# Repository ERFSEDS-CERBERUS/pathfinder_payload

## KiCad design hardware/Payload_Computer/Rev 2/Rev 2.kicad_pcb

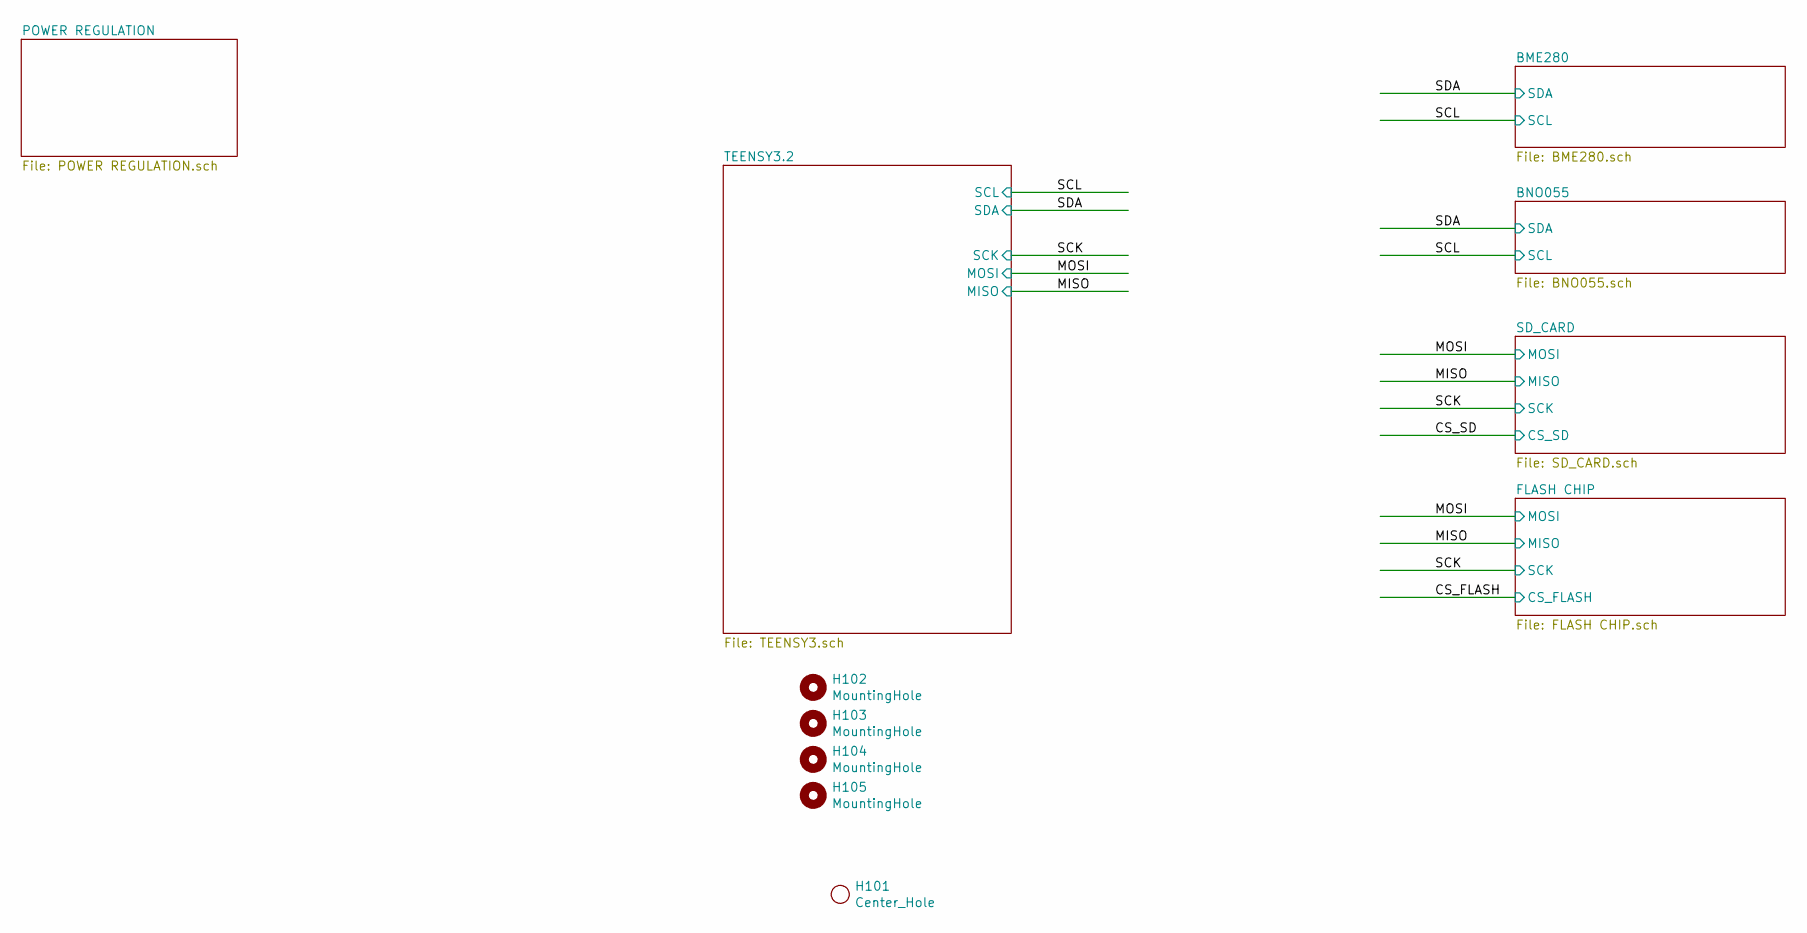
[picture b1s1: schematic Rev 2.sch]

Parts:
H101: Center_Hole; Center_hole
H102, H103, H104, H105: MountingHole; MountingHole_3.5mm

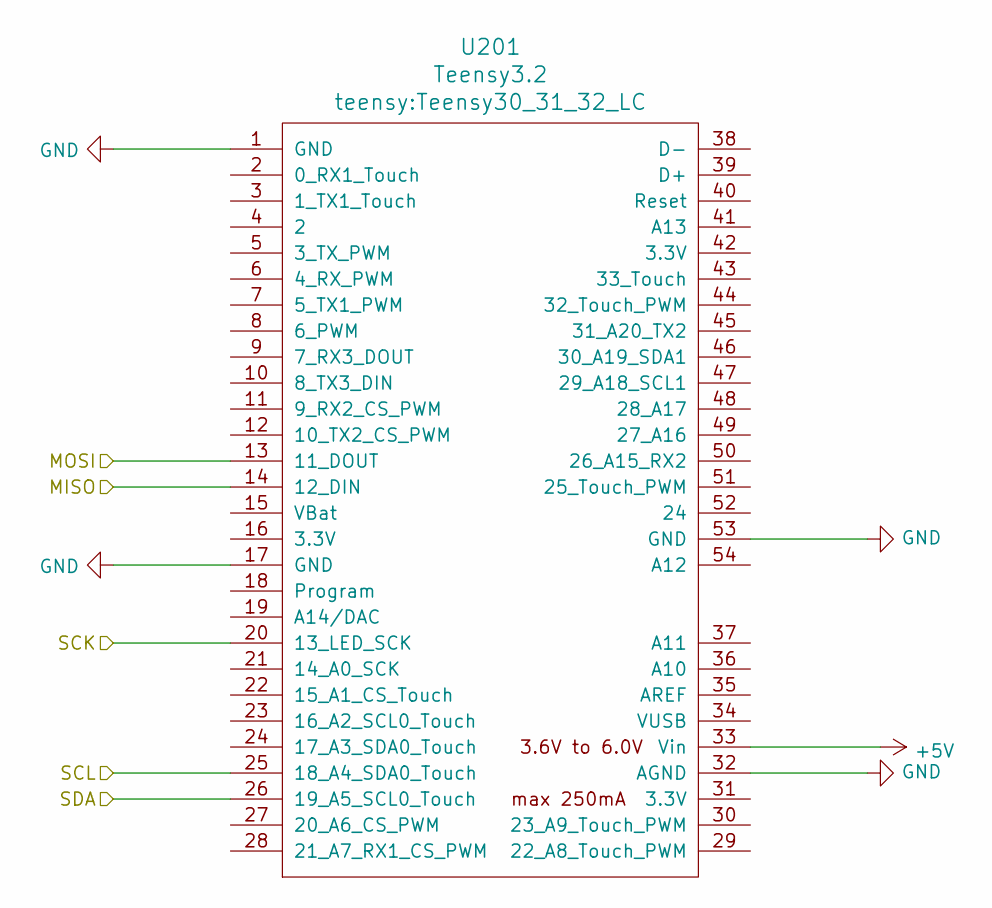
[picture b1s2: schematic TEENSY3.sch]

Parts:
U201: Teensy3.2; Teensy30_31_32_LC

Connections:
+5V: U201.33 (Vin); also elsewhere on the board
/CS_FLASH: U201.22 (15_A1_CS_Touch); also elsewhere on the board
/CS_SD: U201.21 (14_A0_SCK); also elsewhere on the board
/MISO: U201.14 (12_DIN); also elsewhere on the board
/MOSI: U201.13 (11_DOUT); also elsewhere on the board
/SCK: U201.20 (13_LED_SCK); also elsewhere on the board
/SCL: U201.25 (18_A4_SDA0_Touch); also elsewhere on the board
/SDA: U201.26 (19_A5_SCL0_Touch); also elsewhere on the board
GND: U201.1 (GND), U201.17 (GND), U201.32 (AGND), U201.53 (GND); also elsewhere on the board

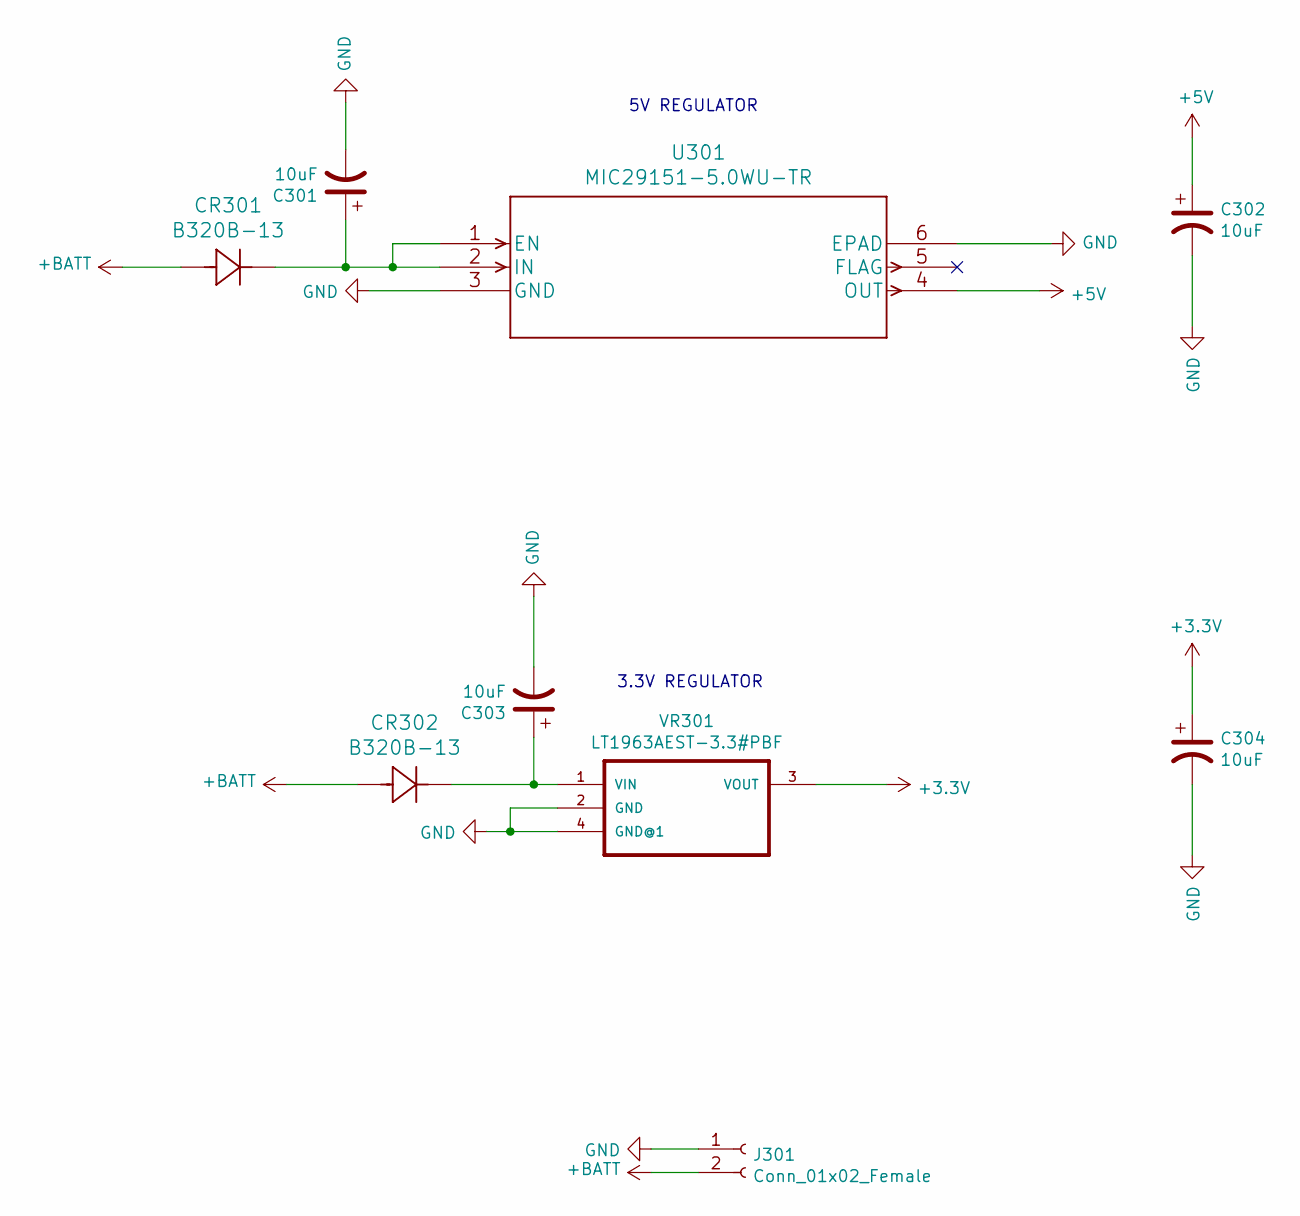
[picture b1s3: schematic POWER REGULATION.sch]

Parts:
C301, C302, C303, C304: 10uF; CP_EIA-6032-20_AVX-F_Pad2.25x2.35mm_HandSolder; DIGIKEY 718-1958-1-ND
CR301, CR302: B320B-13; DIGIKEY B320B-FDICT-ND
J301: Conn_01x02_Female; AMASS_XT30PW-M_1x02_P2.50mm_Horizontal
U301: MIC29151-5.0WU-TR; DIGIKEY MIC29151-5.0WU-TR
VR301: LT1963AEST-3.3#PBF; SOT223; MPN LT1963AEST-3.3#PBF; Digikey LT1963AEST-3.3#PBF-ND

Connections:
+3V3: C304.1, VR301.3 (VOUT); also elsewhere on the board
+5V: C302.1, U301.4 (OUT); also elsewhere on the board
+BATT: CR301.2, CR302.2, J301.2
GND: C301.2, C302.2, C303.2, C304.2, J301.1, U301.3 (GND), U301.6 (EPAD), VR301.2 (GND), VR301.4 (GND@1); also elsewhere on the board
unnamed: C301.1, CR301.1, U301.1 (EN), U301.2 (IN)
unnamed: C303.1, CR302.1, VR301.1 (VIN)

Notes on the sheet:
5V REGULATOR
3.3V REGULATOR

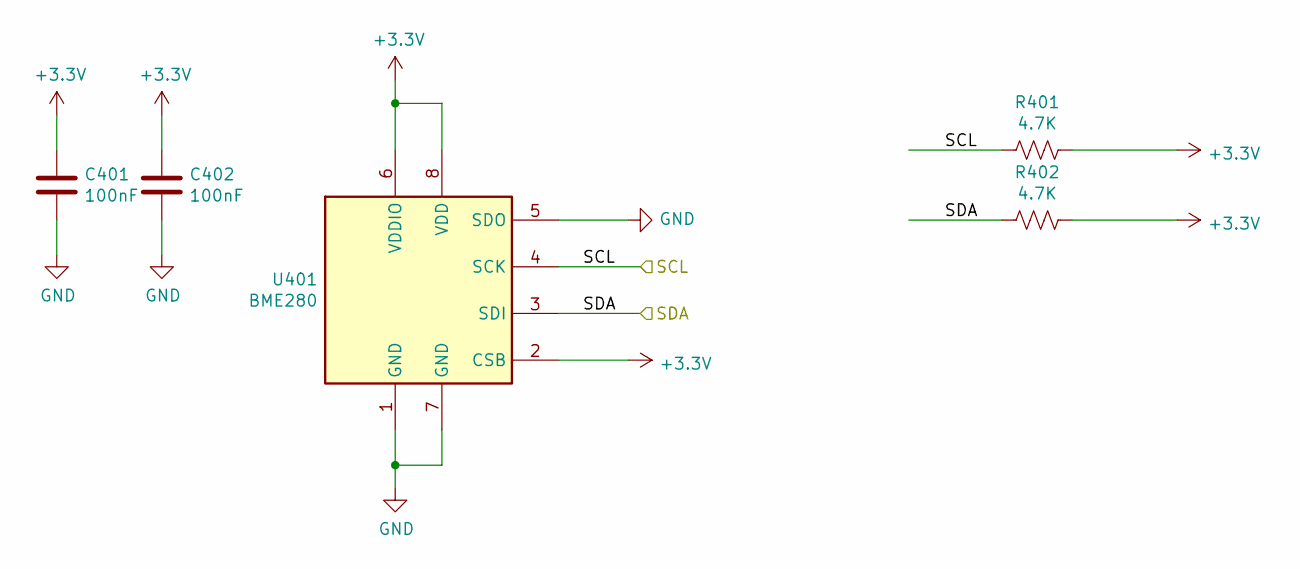
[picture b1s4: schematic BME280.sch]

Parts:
C401, C402: 100nF; C_0603_1608Metric_Pad1.08x0.95mm_HandSolder
R401, R402: 4.7K; R_0603_1608Metric_Pad0.98x0.95mm_HandSolder
U401: BME280; Bosch_LGA-8_2.5x2.5mm_P0.65mm_ClockwisePinNumbering

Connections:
+3V3: C401.1, C402.1, R401.1, R402.1, U401.2 (CSB), U401.6 (VDDIO), U401.8 (VDD); also elsewhere on the board
/SCL: R401.2, U401.4 (SCK); also elsewhere on the board
/SDA: R402.2, U401.3 (SDI); also elsewhere on the board
GND: C401.2, C402.2, U401.1 (GND), U401.5 (SDO), U401.7 (GND); also elsewhere on the board

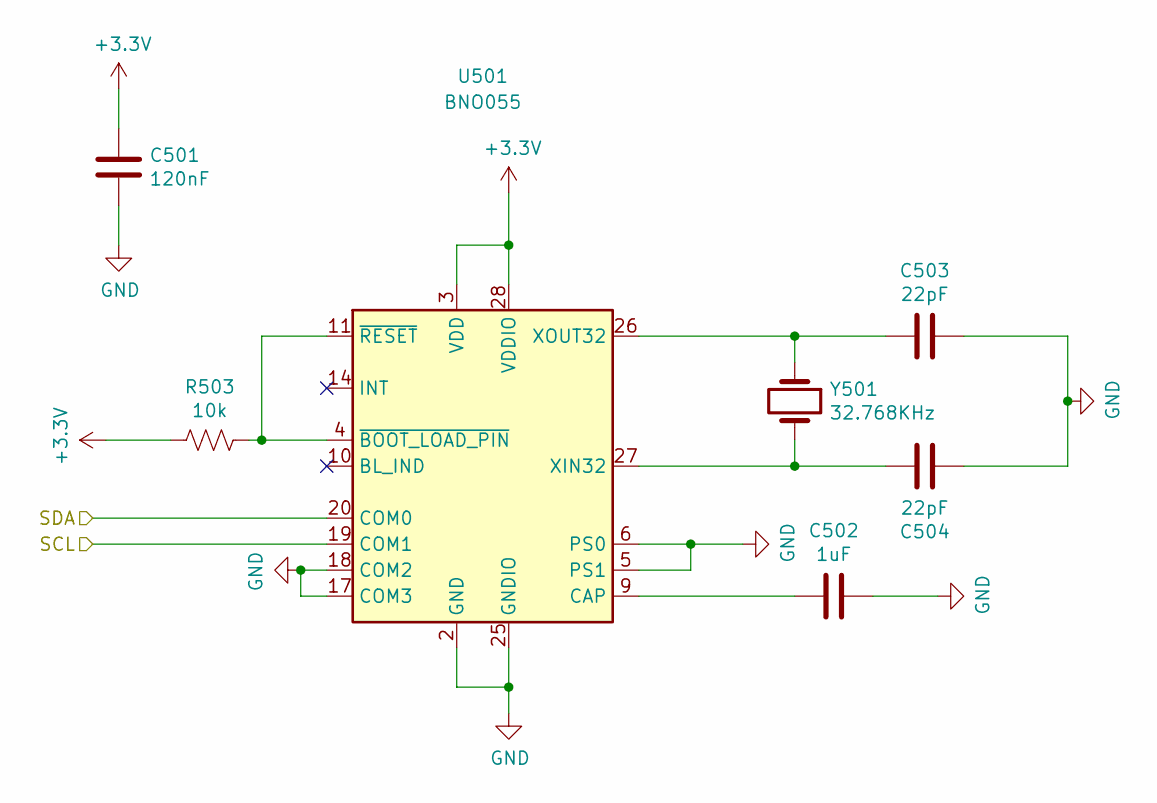
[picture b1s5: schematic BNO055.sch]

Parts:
C501: 120nF; C_0603_1608Metric_Pad1.08x0.95mm_HandSolder
C502: 1uF; C_0603_1608Metric_Pad1.08x0.95mm_HandSolder
C503, C504: 22pF; C_0603_1608Metric_Pad1.08x0.95mm_HandSolder
R503: 10k; R_0603_1608Metric_Pad0.98x0.95mm_HandSolder
U501: BNO055; LGA-28_5.2x3.8mm_P0.5mm
Y501: 32.768KHz; crystal; Digikey 887-1425-1-ND

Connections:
+3V3: C501.1, R503.1, U501.3 (VDD), U501.28 (VDDIO); also elsewhere on the board
/SCL: U501.19 (COM1); also elsewhere on the board
/SDA: U501.20 (COM0); also elsewhere on the board
GND: C501.2, C502.2, C503.1, C504.2, U501.2 (GND), U501.5 (PS1), U501.6 (PS0), U501.15 (GNDIO), U501.16 (GNDIO), U501.17 (COM3), U501.18 (COM2), U501.25 (GNDIO); also elsewhere on the board
unnamed: C502.1, U501.9 (CAP)
unnamed: C503.2, U501.26 (XOUT32), Y501.1
unnamed: C504.1, U501.27 (XIN32), Y501.2
unnamed: R503.2, U501.4 (~BOOT_LOAD_PIN), U501.11 (~RESET)

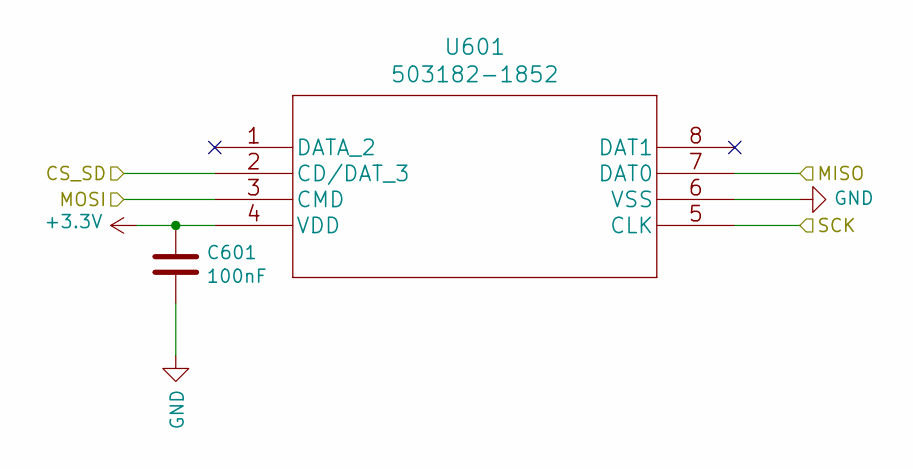
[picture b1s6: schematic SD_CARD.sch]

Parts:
C601: 100nF; C_0603_1608Metric_Pad1.08x0.95mm_HandSolder
U601: 503182-1852

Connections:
+3V3: C601.1, U601.4 (VDD); also elsewhere on the board
/CS_SD: U601.2 (CD/DAT_3); also elsewhere on the board
/MISO: U601.7 (DAT0); also elsewhere on the board
/MOSI: U601.3 (CMD); also elsewhere on the board
/SCK: U601.5 (CLK); also elsewhere on the board
GND: C601.2, U601.6 (VSS); also elsewhere on the board

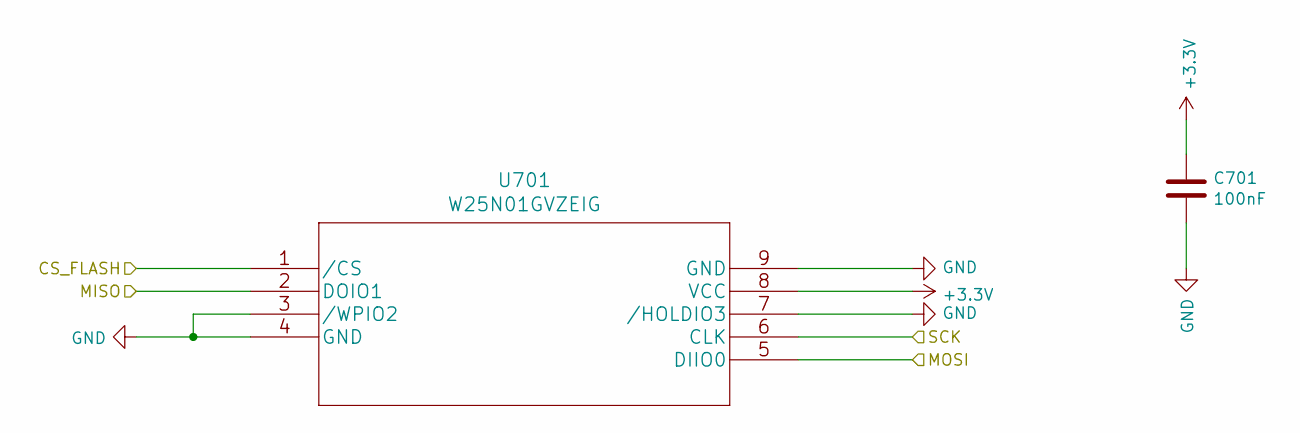
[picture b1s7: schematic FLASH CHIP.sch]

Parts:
C701: 100nF; C_0603_1608Metric_Pad1.08x0.95mm_HandSolder
U701: W25N01GVZEIG

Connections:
+3V3: C701.1, U701.8 (VCC); also elsewhere on the board
/CS_FLASH: U701.1 (/CS); also elsewhere on the board
/MISO: U701.2 (DOIO1); also elsewhere on the board
/MOSI: U701.5 (DIIO0); also elsewhere on the board
/SCK: U701.6 (CLK); also elsewhere on the board
GND: C701.2, U701.3 (/WPIO2), U701.4 (GND), U701.7 (/HOLDIO3), U701.9 (GND); also elsewhere on the board

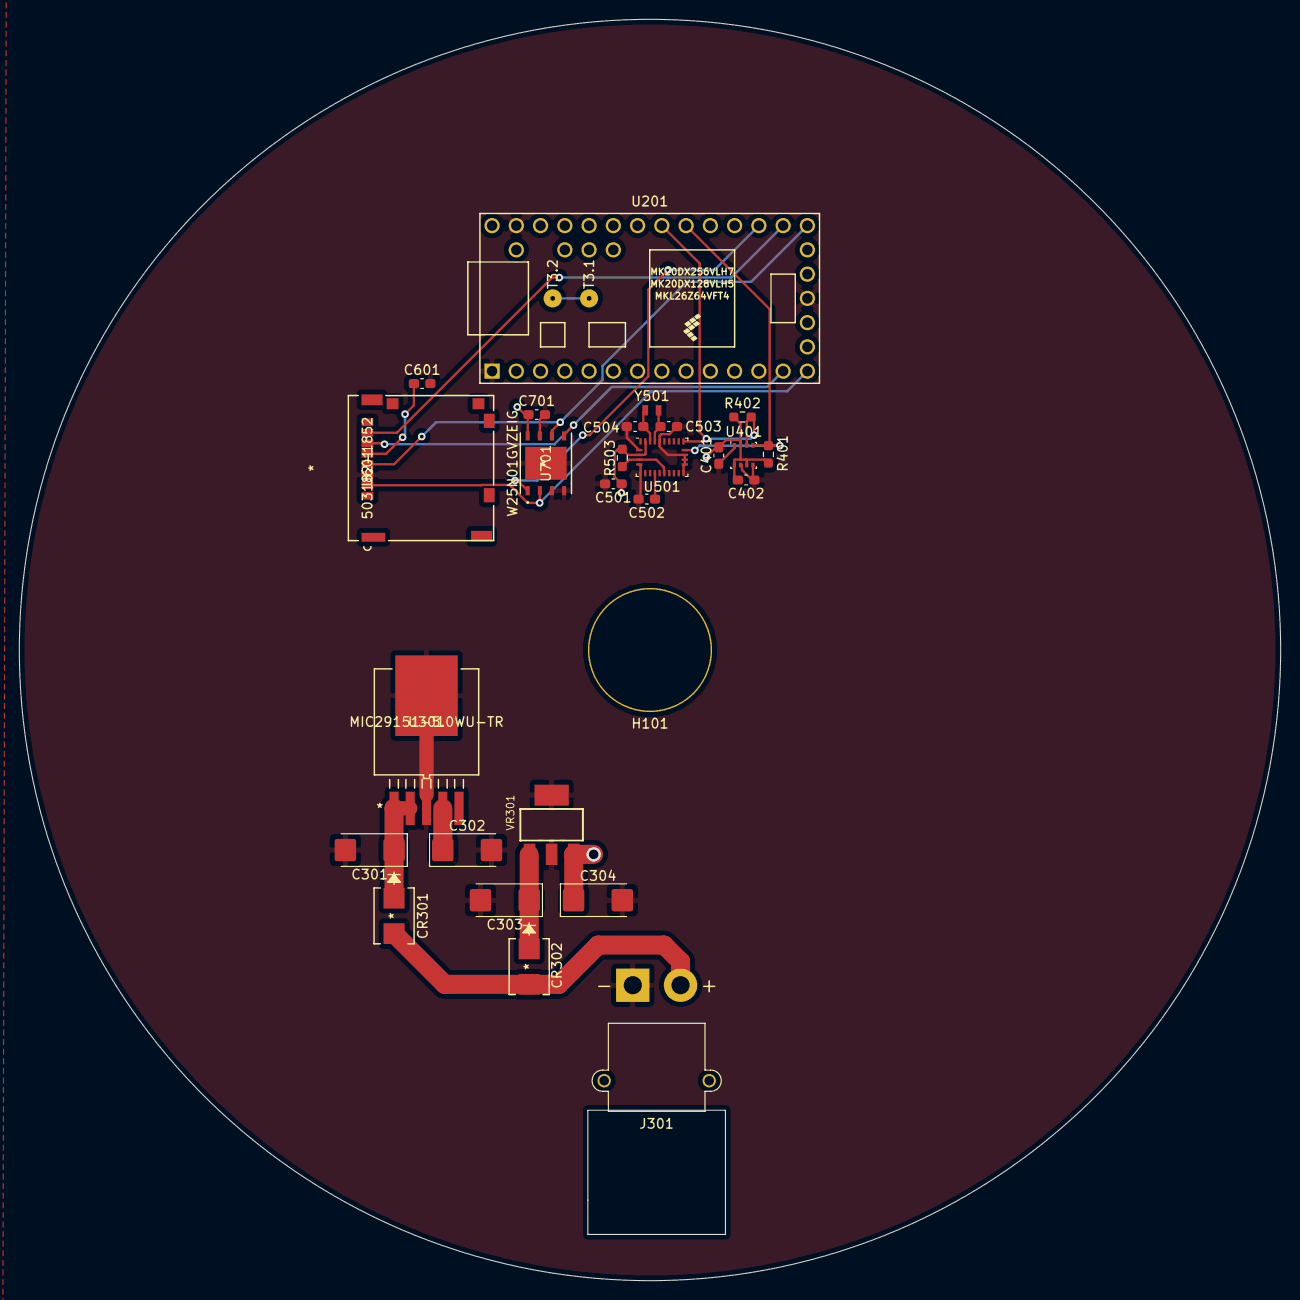
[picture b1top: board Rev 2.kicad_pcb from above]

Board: 2 copper layers, 132.1 x 132.1 mm, 31 parts (0 on the bottom side), 17 nets.

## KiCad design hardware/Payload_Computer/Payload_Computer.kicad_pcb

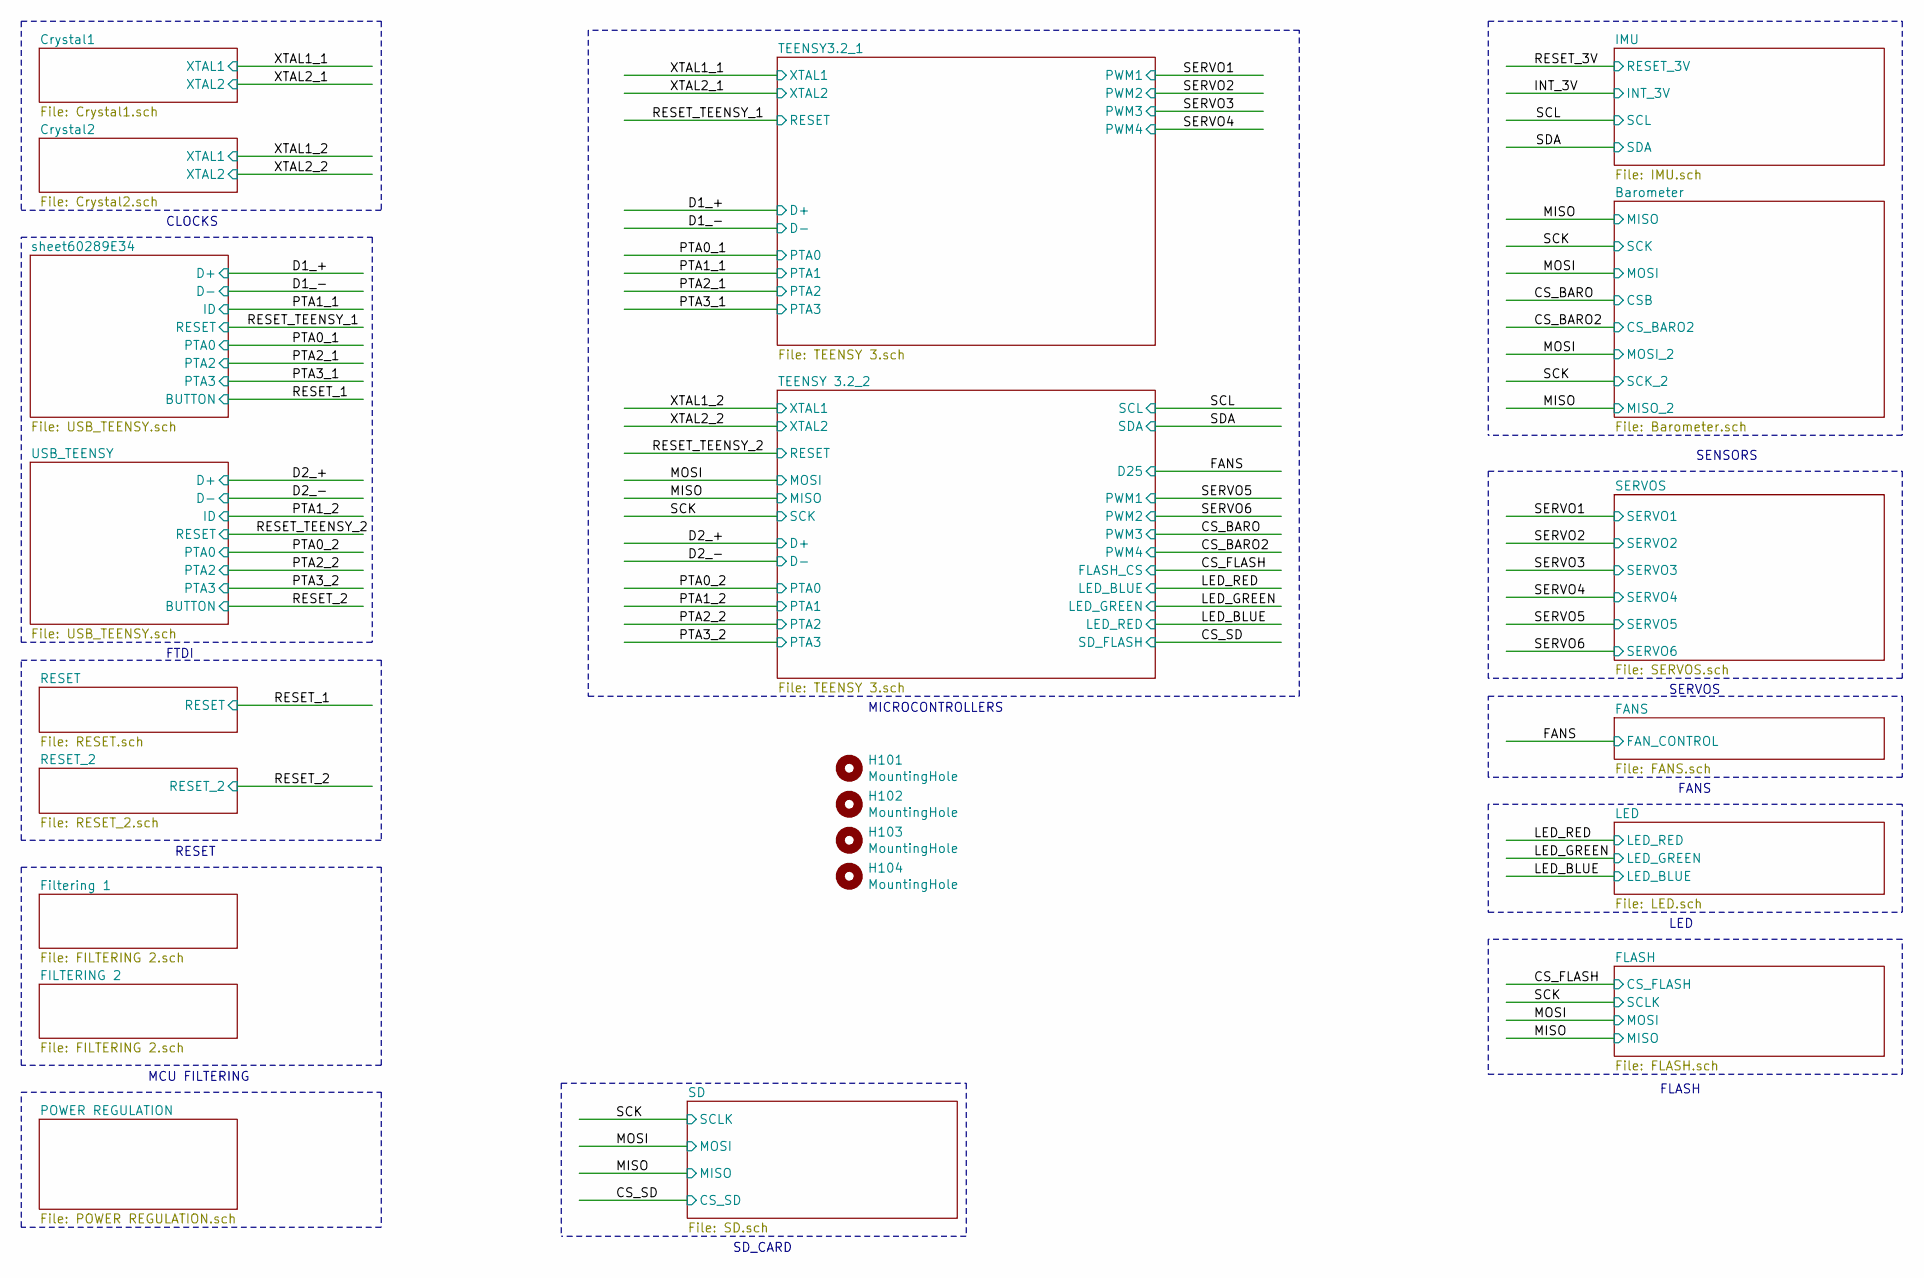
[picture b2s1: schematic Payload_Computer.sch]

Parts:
H101, H102, H103, H104: MountingHole; MountingHole_3.2mm_M3

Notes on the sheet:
CLOCKS
FTDI
RESET
MCU FILTERING
SENSORS
SERVOS
LED
FANS
FLASH
SD_CARD
MICROCONTROLLERS

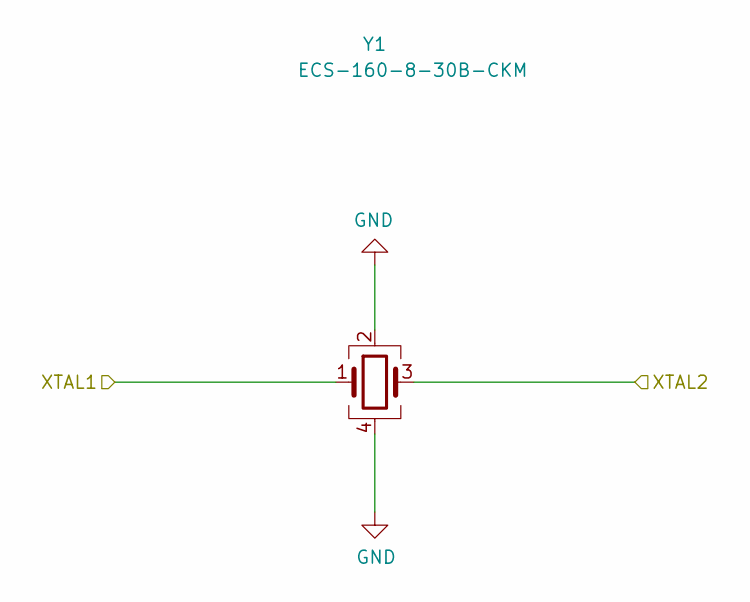
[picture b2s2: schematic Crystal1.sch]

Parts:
Y1: ECS-160-8-30B-CKM; 16Mhz

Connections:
/XTAL1_1: Y1.1; also elsewhere on the board
/XTAL2_1: Y1.3; also elsewhere on the board
GND: Y1.2, Y1.4; also elsewhere on the board

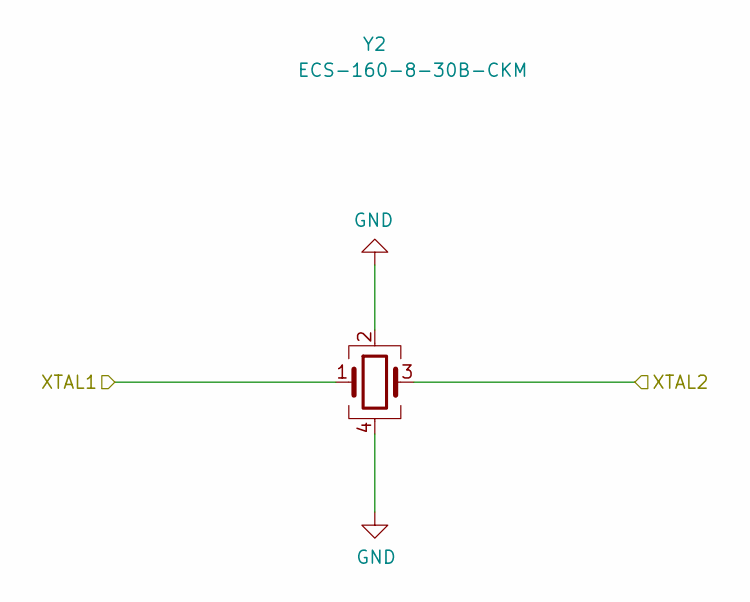
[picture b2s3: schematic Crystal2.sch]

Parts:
Y2: ECS-160-8-30B-CKM; 16Mhz

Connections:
/XTAL1_2: Y2.1; also elsewhere on the board
/XTAL2_2: Y2.3; also elsewhere on the board
GND: Y2.2, Y2.4; also elsewhere on the board

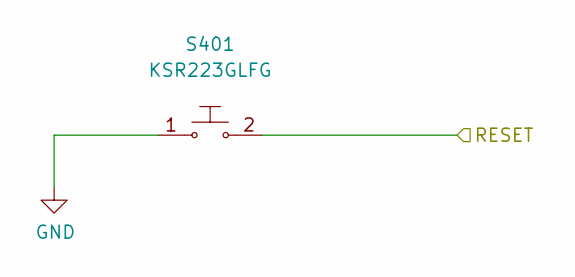
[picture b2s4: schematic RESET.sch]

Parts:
S401: KSR223GLFG; button

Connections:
/RESET_1: S401.2; also elsewhere on the board
GND: S401.1; also elsewhere on the board

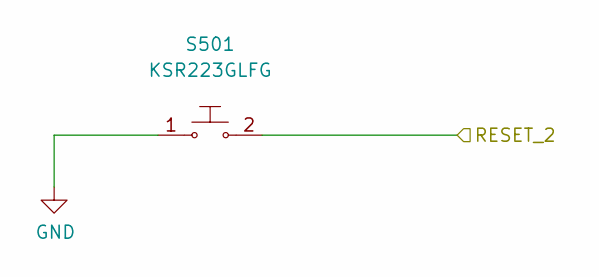
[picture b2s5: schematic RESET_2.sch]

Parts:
S501: KSR223GLFG; button

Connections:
/RESET_2: S501.2; also elsewhere on the board
GND: S501.1; also elsewhere on the board

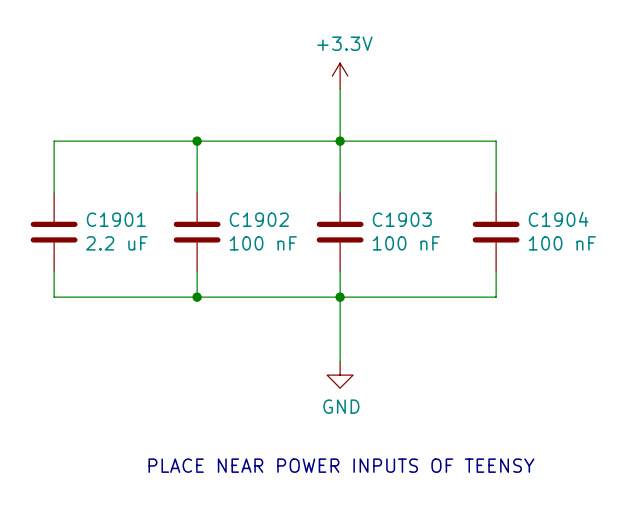
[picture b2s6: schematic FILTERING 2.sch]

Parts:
C18, C20, C602: 100 nF; C_0603_1608Metric_Pad1.08x0.95mm_HandSolder
C601: 2.2 uF; C_0603_1608Metric_Pad1.08x0.95mm_HandSolder

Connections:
+3V3: C18.1, C20.1, C601.1, C602.1; also elsewhere on the board
GND: C18.2, C20.2, C601.2, C602.2; also elsewhere on the board

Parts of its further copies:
C1901: 2.2 uF; C_0603_1608Metric_Pad1.08x0.95mm_HandSolder
C1902, C1903, C1904: 100 nF; C_0603_1608Metric_Pad1.08x0.95mm_HandSolder

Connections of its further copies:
+3V3: C1901.1, C1902.1, C1903.1, C1904.1; also elsewhere on the board
GND: C1901.2, C1902.2, C1903.2, C1904.2; also elsewhere on the board

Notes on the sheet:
PLACE NEAR POWER INPUTS OF TEENSY

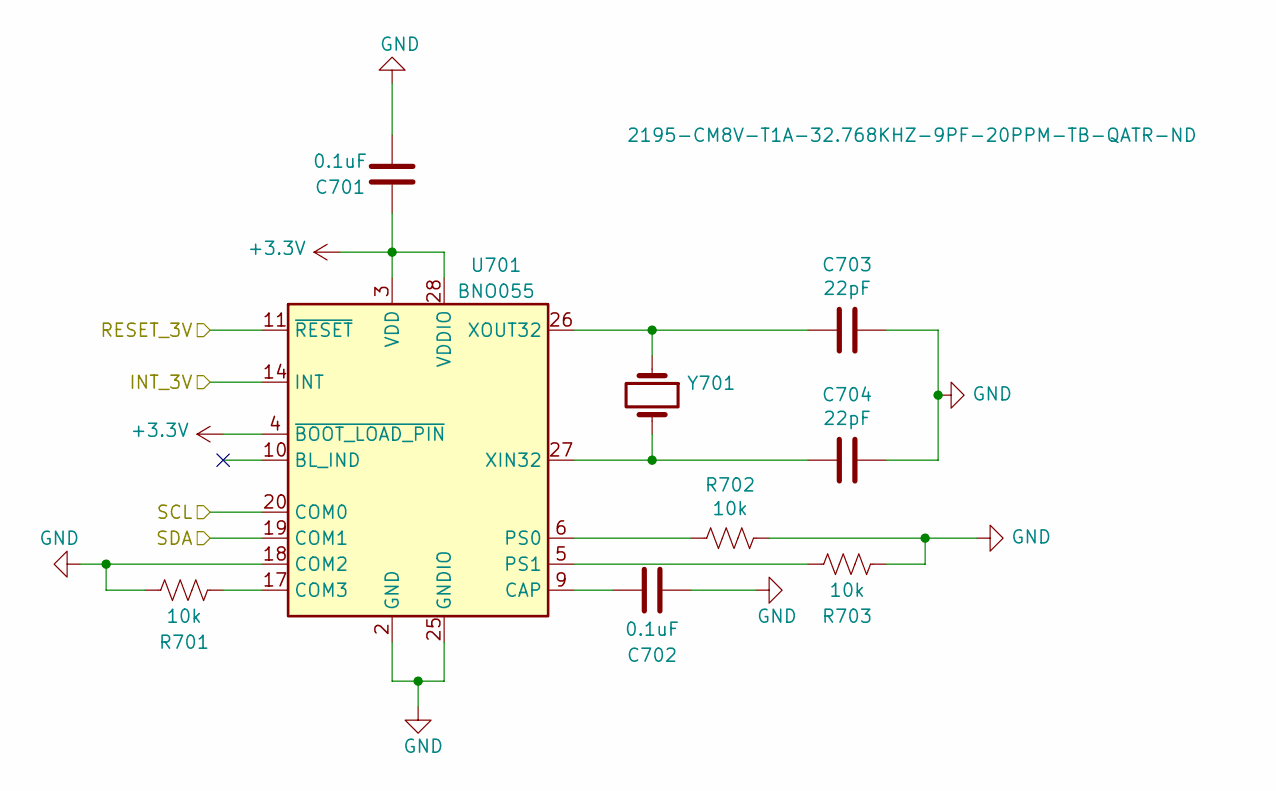
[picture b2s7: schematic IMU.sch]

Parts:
C701, C702: 0.1uF; C_0603_1608Metric_Pad1.08x0.95mm_HandSolder
C703, C704: 22pF; C_0603_1608Metric_Pad1.08x0.95mm_HandSolder
R701, R702, R703: 10k; R_0603_1608Metric_Pad0.98x0.95mm_HandSolder
U701: BNO055; LGA-28_5.2x3.8mm_P0.5mm
Y701: 2195-CM8V-T1A-32.768KHZ-9PF-20PPM-TB-QATR-ND; 32khz

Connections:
+3V3: C701.1, U701.3 (VDD), U701.4 (~BOOT_LOAD_PIN), U701.28 (VDDIO); also elsewhere on the board
/INT_3V: U701.14 (INT)
/RESET_3V: U701.11 (~RESET)
/SCL: U701.20 (COM0); also elsewhere on the board
/SDA: U701.19 (COM1); also elsewhere on the board
GND: C701.2, C702.1, C703.1, C704.1, R701.2, R702.1, R703.1, U701.2 (GND), U701.15 (GNDIO), U701.16 (GNDIO), U701.18 (COM2), U701.25 (GNDIO); also elsewhere on the board
unnamed: C702.2, U701.9 (CAP)
unnamed: C703.2, U701.26 (XOUT32), Y701.1
unnamed: C704.2, U701.27 (XIN32), Y701.2
unnamed: R701.1, U701.17 (COM3)
unnamed: R702.2, U701.6 (PS0)
unnamed: R703.2, U701.5 (PS1)

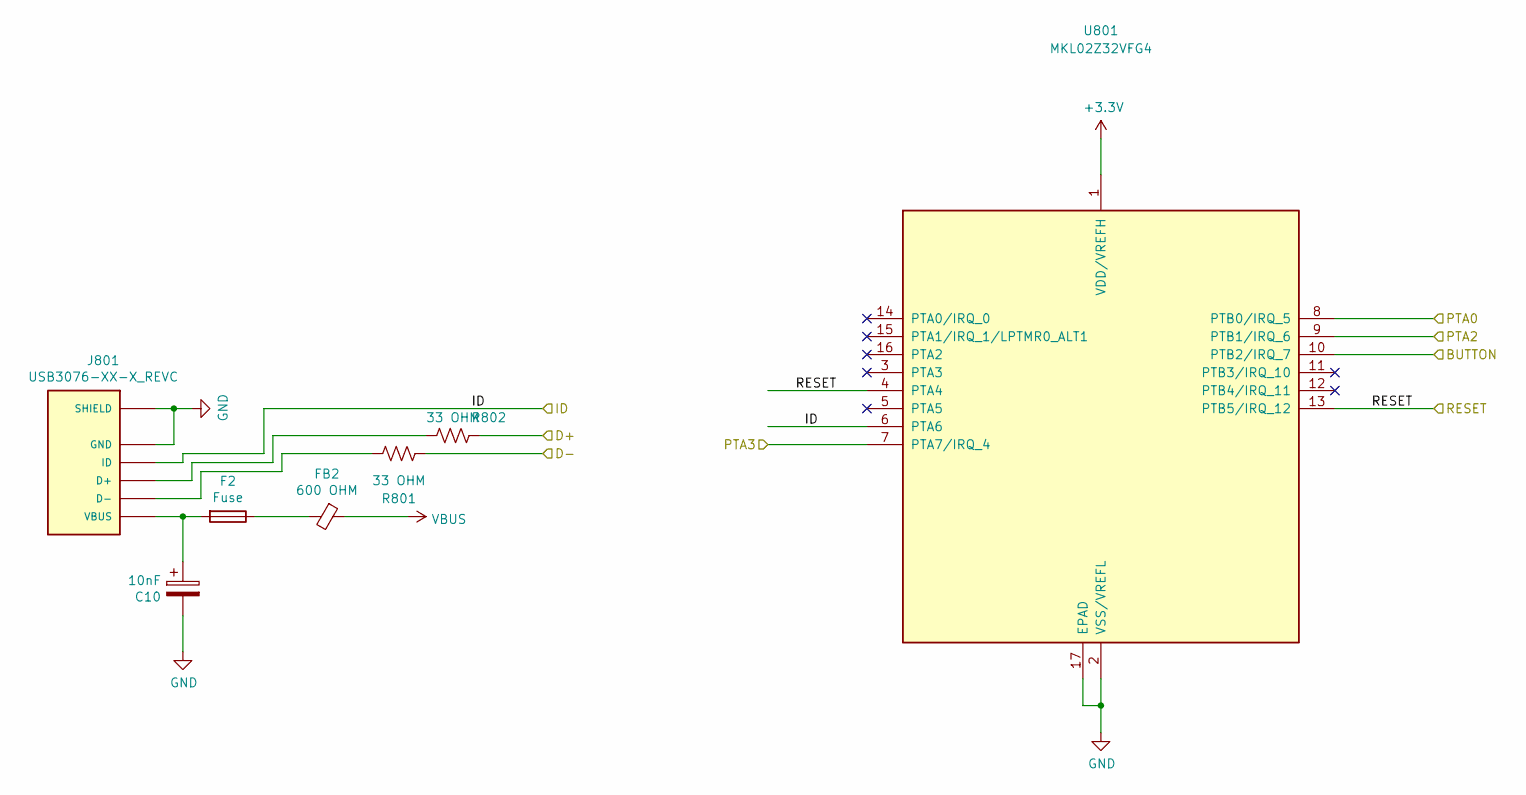
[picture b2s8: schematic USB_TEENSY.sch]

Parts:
C10: 10nF; C_0603_1608Metric_Pad1.08x0.95mm_HandSolder
F2: Fuse; Fuse_0603_1608Metric_Pad1.05x0.95mm_HandSolder
FB2: 600 OHM; C_0603_1608Metric_Pad1.08x0.95mm_HandSolder
J1201: USB3076-XX-X_REVC; GCT_USB3076-XX-X_REVC
R801, R802: 33 OHM; R_0603_1608Metric_Pad0.98x0.95mm_HandSolder
U801: MKL02Z32VFG4; QFN-16-1EP_3x3mm_P0.5mm_EP1.9x1.9mm

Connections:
+3V3: U801.1 (VDD/VREFH); also elsewhere on the board
/D2_+: R802.1; also elsewhere on the board
/D2_-: R801.1; also elsewhere on the board
/PTA0_2: U801.8 (PTB0/IRQ_5); also elsewhere on the board
/PTA2_2: U801.9 (PTB1/IRQ_6); also elsewhere on the board
/PTA3_2: U801.7 (PTA7/IRQ_4); also elsewhere on the board
/RESET_2: U801.10 (PTB2/IRQ_7); also elsewhere on the board
/RESET_TEENSY_2: U801.4 (PTA4), U801.13 (PTB5/IRQ_12); also elsewhere on the board
GND: C10.2, J1201.5 (GND), J1201.6 (SHIELD), J1201.7 (SHIELD), J1201.8 (SHIELD), J1201.9 (SHIELD), J1201.10 (SHIELD), J1201.11 (SHIELD), U801.2 (VSS/VREFL), U801.17 (EPAD); also elsewhere on the board
unnamed: F2.1, FB2.2
VBUS: FB2.1; also elsewhere on the board

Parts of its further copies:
C1801: 10nF; C_0603_1608Metric_Pad1.08x0.95mm_HandSolder
F1801: Fuse; Fuse_0603_1608Metric_Pad1.05x0.95mm_HandSolder
FB1801: 600 OHM; C_0603_1608Metric_Pad1.08x0.95mm_HandSolder
J801: USB3076-XX-X_REVC; GCT_USB3076-XX-X_REVC
R1801, R1802: 33 OHM; R_0603_1608Metric_Pad0.98x0.95mm_HandSolder
U1801: MKL02Z32VFG4; QFN-16-1EP_3x3mm_P0.5mm_EP1.9x1.9mm

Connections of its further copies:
+3V3: U1801.1 (VDD/VREFH); also elsewhere on the board
/D1_+: R1802.1; also elsewhere on the board
/D1_-: R1801.1; also elsewhere on the board
/PTA0_1: U1801.8 (PTB0/IRQ_5); also elsewhere on the board
/PTA2_1: U1801.9 (PTB1/IRQ_6); also elsewhere on the board
/PTA3_1: U1801.7 (PTA7/IRQ_4); also elsewhere on the board
/RESET_1: U1801.10 (PTB2/IRQ_7); also elsewhere on the board
/RESET_TEENSY_1: U1801.4 (PTA4), U1801.13 (PTB5/IRQ_12); also elsewhere on the board
GND: C1801.2, J801.5 (GND), J801.6 (SHIELD), J801.7 (SHIELD), J801.8 (SHIELD), J801.9 (SHIELD), J801.10 (SHIELD), J801.11 (SHIELD), U1801.2 (VSS/VREFL), U1801.17 (EPAD); also elsewhere on the board
unnamed: F1801.1, FB1801.2
VBUS: FB1801.1; also elsewhere on the board

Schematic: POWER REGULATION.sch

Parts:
C904: 10uF; C_0603_1608Metric_Pad1.08x0.95mm_HandSolder; Digikey 1276-1948-2-ND
C905: 100uF; C_0805_2012Metric_Pad1.18x1.45mm_HandSolder; Digikey 490-13981-2-ND
D902: SDM2U40CSP-7B; DIO_SDM2U40CSP-7B; PARTREV 5-2
IC901: ZLDO1117G33TA; SOT230P700X180-4N; Manufacturer_Part_Number ZLDO1117G33TA; Mouser Part Number 522-ZLDO1117G33TA
J901: Conn_01x02_Male; AMASS_XT30PW-M_1x02_P2.50mm_Horizontal

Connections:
+3V3: C905.1, IC901.2 (VOUT_1), IC901.4 (VOUT_2); also elsewhere on the board
+BATT: C904.1, D902.C, IC901.3 (VIN), J901.1; also elsewhere on the board
GND: C904.2, C905.2, IC901.1 (ADJ(GND)), J901.2; also elsewhere on the board
VBUS: D902.A; also elsewhere on the board

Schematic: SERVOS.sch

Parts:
C1001, C1002, C1003, C1004, C1009, C1010: 0.47 uF; C_0603_1608Metric_Pad1.08x0.95mm_HandSolder
C1005, C1006, C1007, C1008, C1011, C1012: 22 uF; C_0603_1608Metric_Pad1.08x0.95mm_HandSolder; Digikey 1276-2868-2-ND
J1001, J1002, J1003, J1004, J1005, J1006: 505567-0381; 5055670381; Manufacturer_Part_Number 505567-0381; Mouser Part Number 538-505567-0381
VR1001, VR1002, VR1003, VR1004, VR1005, VR1006: LM2940IMP-5.0_NOPB; SOT230P700X180-4N; PARTREV J

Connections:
+BATT: C1001.1, C1002.1, C1003.1, C1004.1, C1009.1, C1010.1, VR1001.1 (IN), VR1002.1 (IN), VR1003.1 (IN), VR1004.1 (IN), VR1005.1 (IN), VR1006.1 (IN); also elsewhere on the board
/SERVO1: J1001.1; also elsewhere on the board
/SERVO2: J1002.1; also elsewhere on the board
/SERVO3: J1003.1; also elsewhere on the board
/SERVO4: J1004.1; also elsewhere on the board
/SERVO5: J1005.1; also elsewhere on the board
/SERVO6: J1006.1; also elsewhere on the board
/SERVOS/SERVO_5V_1: C1005.1, J1001.3, VR1001.3 (OUT)
/SERVOS/SERVO_5V_2: C1006.1, J1002.3, VR1002.3 (OUT)
/SERVOS/SERVO_5V_3: C1007.1, J1003.3, VR1003.3 (OUT)
/SERVOS/SERVO_5V_4: C1008.1, C1011.1, C1012.1, J1004.3, J1005.3, J1006.3, VR1004.3 (OUT), VR1005.3 (OUT), VR1006.3 (OUT)
GND: C1001.2, C1002.2, C1003.2, C1004.2, C1005.2, C1006.2, C1007.2, C1008.2, C1009.2, C1010.2, C1011.2, C1012.2, J1001.2, J1001.MP1, J1001.MP2, J1002.2, J1002.MP1, J1002.MP2, J1003.2, J1003.MP1, J1003.MP2, J1004.2, J1004.MP1, J1004.MP2, J1005.2, J1005.MP1, J1005.MP2, J1006.2, J1006.MP1, J1006.MP2, VR1001.2 (GND_2), VR1001.4 (GND_4), VR1002.2 (GND_2), VR1002.4 (GND_4), VR1003.2 (GND_2), VR1003.4 (GND_4), VR1004.2 (GND_2), VR1004.4 (GND_4), VR1005.2 (GND_2), VR1005.4 (GND_4), VR1006.2 (GND_2), VR1006.4 (GND_4); also elsewhere on the board

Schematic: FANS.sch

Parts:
C1101: 0.47 uF; C_0603_1608Metric_Pad1.08x0.95mm_HandSolder
C1102: 22uF; C_0603_1608Metric_Pad1.08x0.95mm_HandSolder
D1601: SDM2U40CSP-7B; DIO_SDM2U40CSP-7B; PARTREV 5-2
J1601, J1602, J1603, J1604: 0532610271; MOLEX_0532610271; PARTREV J
Q1601: FDT439; SOT-223-3_TabPin2
R1601: 10K; R_0603_1608Metric_Pad0.98x0.95mm_HandSolder
VR1101: LM2940IMP-5.0_NOPB; SOT230P700X180-4N; PARTREV J

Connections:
+5V: C1102.1, Q1601.2 (D), VR1101.3 (OUT)
+BATT: C1101.1, VR1101.1 (IN); also elsewhere on the board
/FANS: Q1601.1 (G), R1601.1; also elsewhere on the board
/FANS/FANS: D1601.C, J1601.1, J1602.1, J1603.1, J1604.1
GND: C1101.2, C1102.2, J1601.2, J1601.S1 (SHIELD), J1601.S2 (SHIELD), J1602.2, J1602.S1 (SHIELD), J1602.S2 (SHIELD), J1603.2, J1603.S1 (SHIELD), J1603.S2 (SHIELD), J1604.2, J1604.S1 (SHIELD), J1604.S2 (SHIELD), R1601.2, VR1101.2 (GND_2), VR1101.4 (GND_4); also elsewhere on the board
unnamed: D1601.A, Q1601.3 (S)

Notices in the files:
parts and their libraries:
Copyright 2016 Accelerated Designs. All rights reserved.
